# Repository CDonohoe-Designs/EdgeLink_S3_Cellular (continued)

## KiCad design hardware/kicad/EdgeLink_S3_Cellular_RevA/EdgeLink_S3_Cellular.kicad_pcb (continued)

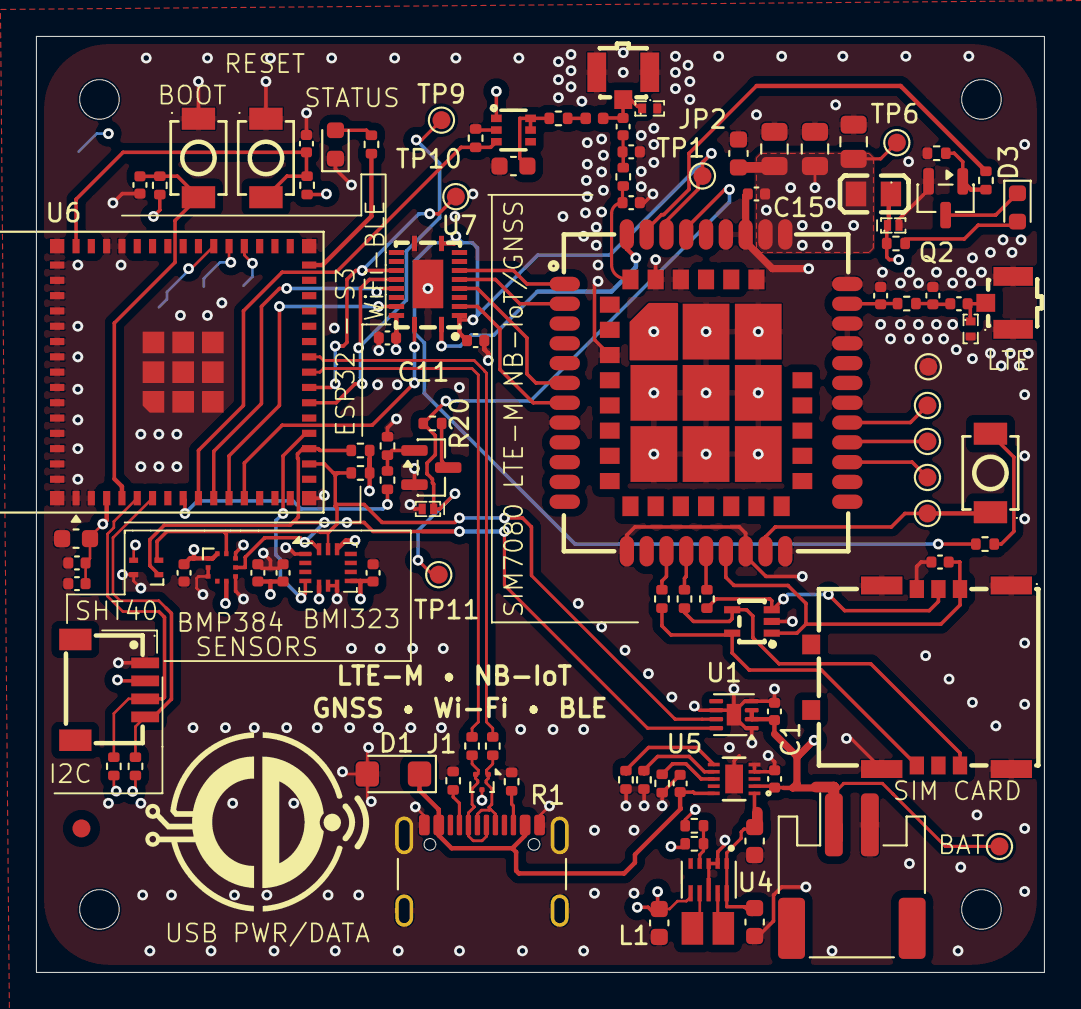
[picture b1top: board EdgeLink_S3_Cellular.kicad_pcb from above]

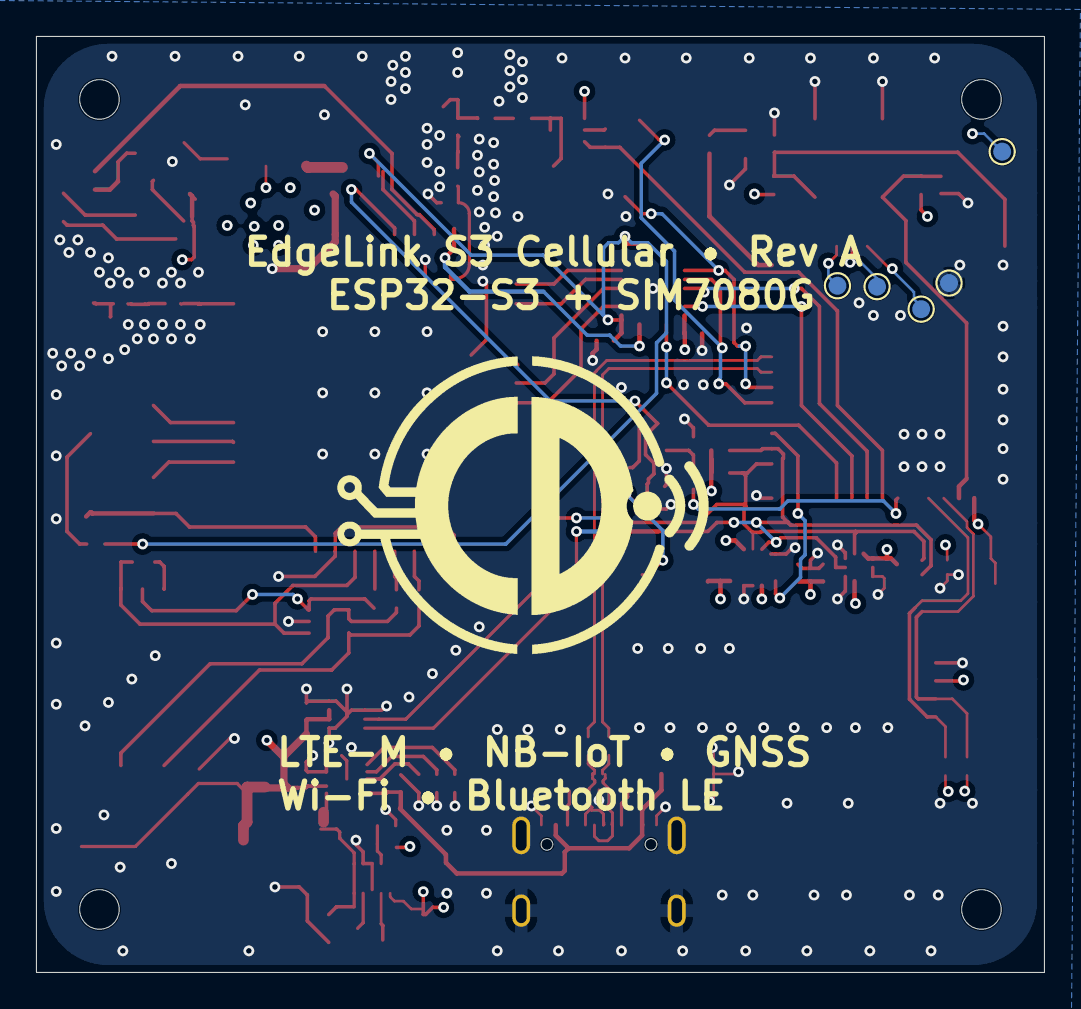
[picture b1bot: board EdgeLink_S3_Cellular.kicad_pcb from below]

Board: 4 copper layers, 56.0 x 52.0 mm, 109 parts (5 on the bottom side), 70 nets.
